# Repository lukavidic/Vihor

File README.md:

# Vihor

Autonomna mobilna platforma sa integrisanim elektromagnetskim topom. Vozilo se zasniva na JoyCar platformi (Joy-IT), a naša ploča (PCB) zamjenjuje micro:bit i upravlja kretanjem, senzorima, topom i WiFi komunikacijom. Vozilo autonomno traži i gađa pokretnu metu na suparničkom vozilu istog tipa, izbjegava prepreke, a START/STOP i log poruke ide preko WiFi-ja do aplikacije na računaru.

Projekat iz računarske elektronike (RE/MKS 26/27).

## Sistem u kratkim crtama

| Dio | Opis |
|---|---|
| Mikrokontroler | PIC24FJ64GA702 |
| WiFi | ESP8266 (ESP-01), AT komande preko UART-a |
| Senzori | HC-SR04 (prepreke), IR Distance Click (meta) |
| Vozilo | JoyCar (motori i drajveri na JoyCar ploči, I2C) |
| Napajanje | 4 × AA baterije, naponi sa zaglavlja JoyCar ploče |
| Top | Elektromagnetski top (coilgun), još nije isporučen |
| Aplikacija | Java (JavaFX), TCP server, komande START i STOP, prikaz logova |

## Dokumentacija

| Dokument | Sadržaj |
|---|---|
| [Specifikacija zahtjeva](docs/Specifikacija-zahtjeva.md) | Funkcionalni i nefunkcionalni zahtjevi, mašine stanja, format logova |
| [HW/SW interfejs](docs/architecture/hwsw-interface.md) | Napajanje, pinovi mikrokontrolera, JoyCar interfejs, komunikacioni protokol |
| [Hardverska arhitektura](docs/architecture/hardware.md) | Blok dijagram, napajanje, konektori, mjerenja |
| [Softverska arhitektura](docs/architecture/software.md) | Moduli firmvera, mašine stanja, aplikacija |
| [Spisak komponenti](docs/components.md) | Sve komponente sa slikama i osnovnim podacima |
| [Električna šema (PDF)](docs/Vihor.pdf) | Svi listovi šeme: naslovni list, blok šema i moduli |

## Organizacija rada

- Zadaci se vode na GitHub Projects tabli **Vihor SCRUM Board**, svaki zadatak je issue sa labelom `hardware` ili `software`.
- Grana `main` sadrži stabilnu verziju, a rad se objedinjuje u granu `dev`.
- Za svaki zadatak se pravi nova grana iz `dev`, imenovana kao `<broj-issuea>-kratak-opis` (npr. `3-hardverska-arhitektura-sistema`).
- Izmjene idu preko Pull Requesta prema `dev`, uz pregled barem jedne osobe. U opisu se navodi `Refs #<broj>`, a issue se zatvara ručno kad je zadatak gotov.
- Dokumenti nose broj verzije u zaglavlju, a ne u imenu grane ili fajla.

## Struktura repozitorija

```
.
├── README.md
├── LICENSE
├── .gitattributes              podešavanja gita za KiCad fajlove
├── .github/                    šabloni za issue i pull request
├── docs/
│   ├── Specifikacija-zahtjeva.md
│   ├── components.md
│   ├── Vihor.pdf               električna šema (svi listovi)
│   ├── images/                 slike komponenti
│   ├── resources/              dijagrami (mašine stanja, aktivnosti)
│   └── architecture/
│       ├── hwsw-interface.md
│       ├── hardware.md
│       └── software.md
├── hardware/
│   ├── Vihor/                  KiCad projekat (šema i ploča)
│   └── libs/                   simboli, footprinti i 3D modeli (PIC, ESP-01, ivični konektor)
└── firmware/
    └── tests/                  testni programi za EasyPIC i TCP server za test na računaru
```

Aplikacija dobija svoj folder (npr. `app/`) kad se doda u repozitorij.

## Stanje projekta

- **Dokumentacija:** specifikacija zahtjeva, HW/SW interfejs, hardverska arhitektura i spisak komponenti su usklađeni sa šemom i rezultatima mjerenja. 
- **Šema:** pripremljena za izradu ploče (PR #47); vrijednosti dijelova za top (R5, R7, D1, F1) još nisu određene.
- **Ispitivanje dijelova:** na razvojnoj ploči EasyPIC Fusion v7 (umjesto našeg PIC-a) ispitani su ESP-01 (AT komande, WiFi, TCP, START i STOP), motori preko I2C i servo motor; testni programi su u `firmware/tests/`. IR senzor je izmjeren multimetrom (napon izlaza u zavisnosti od udaljenosti), a kod ultrazvučnog senzora su izmjereni signali TRIG i ECHO na JoyCar ploči. Rezultati su u `docs/architecture/hwsw-interface.md`.
- **Top:** još nije isporučen; interfejs je predviđen na ploči.

## Licenca

Vidi [LICENSE](LICENSE).

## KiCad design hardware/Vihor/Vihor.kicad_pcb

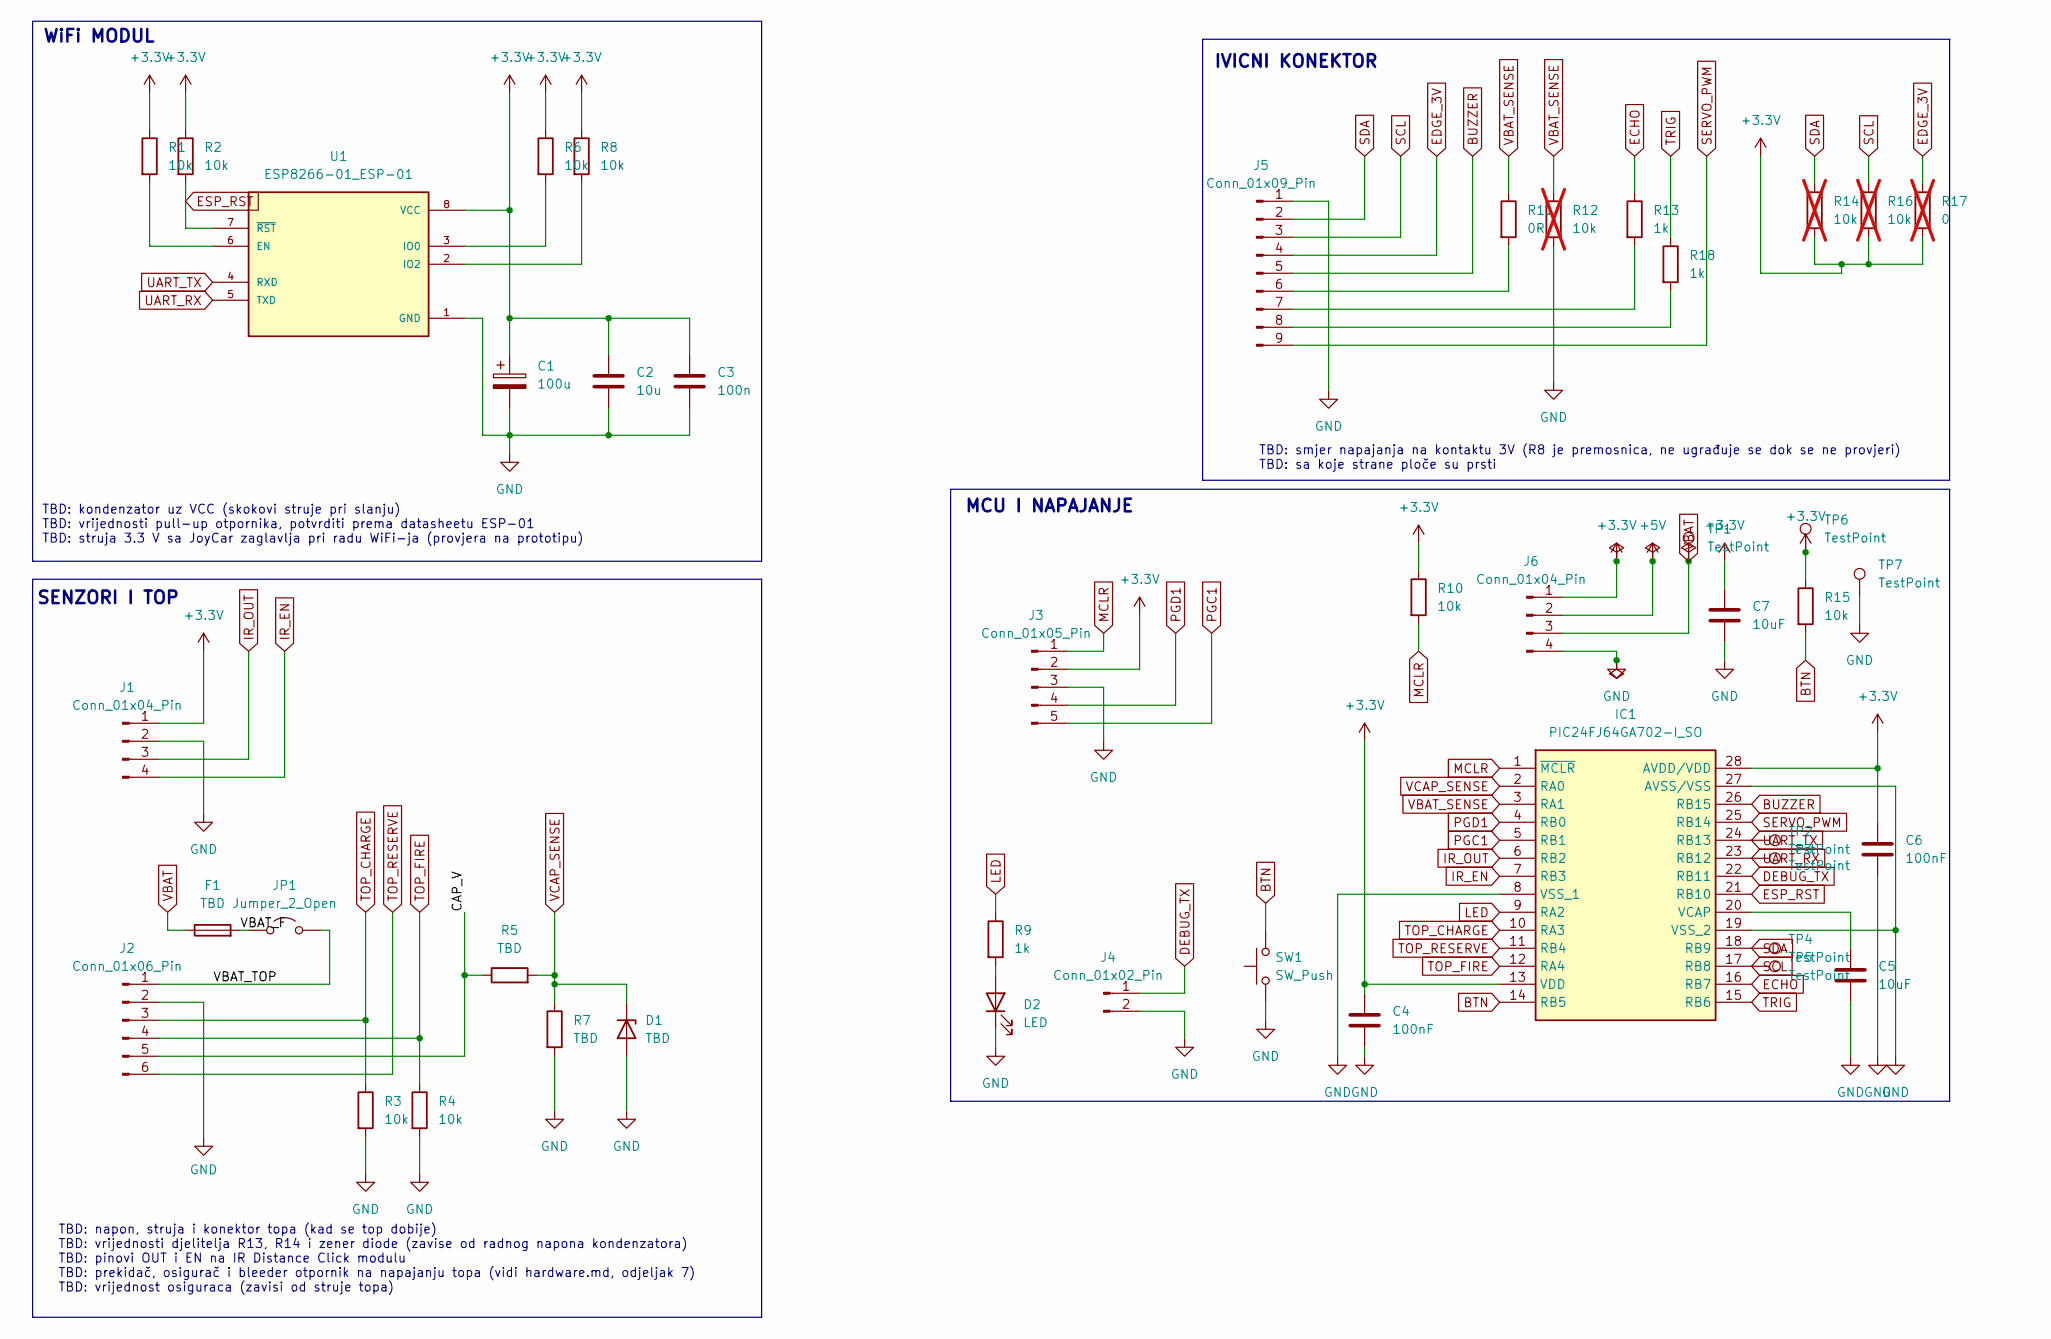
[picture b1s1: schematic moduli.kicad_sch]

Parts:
C1: 100u; CP_Radial_D6.3mm_P2.50mm
C2: 10u; C_0805_2012Metric
C3: 100n; C_0805_2012Metric
C4, C6: 100nF; C_0805_2012Metric
C5, C7: 10uF; C_0805_2012Metric
D1: TBD; D_SOD-123
D2: LED; LED_0805_2012Metric
F1: TBD; Fuse_1206_3216Metric
IC1: PIC24FJ64GA702-I_SO; SOIC127P1030X265-28N; Mouser Part Number 579-24FJ64GA702ISO
J1, J6: Conn_01x04_Pin; PinHeader_1x04_P2.54mm_Vertical
J2: Conn_01x06_Pin; PinHeader_1x06_P2.54mm_Vertical
J3: Conn_01x05_Pin; PinHeader_1x05_P2.54mm_Vertical
J4: Conn_01x02_Pin; PinHeader_1x02_P2.54mm_Vertical
J5: Conn_01x09_Pin; MicroBit_EdgeFingers_9
JP1: Jumper_2_Open; PinHeader_1x02_P2.54mm_Vertical
R1, R2, R3, R4, R6, R8, R10, R15: 10k; R_0805_2012Metric
R5, R7: TBD; R_0805_2012Metric
R9, R13, R18: 1k; R_0805_2012Metric
R11: 0R; R_0805_2012Metric
R12, R14, R16: 10k; R_0805_2012Metric; not fitted
R17: 0; R_0805_2012Metric; not fitted
SW1: SW_Push; SW_PUSH_6mm
TP1, TP2, TP3, TP4, TP5, TP6: TestPoint; TestPoint_Pad_D1.5mm
TP7: TestPoint; TestPoint_THTPad_D2.0mm_Drill1.0mm
U1: ESP8266-01_ESP-01; ESP-01_Socket_2x04_P2.54mm; PARTREV V1.2

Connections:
+3.3V: C1.1, C2.1, C3.1, C4.1, C6.1, C7.1, IC1.13 (VDD), IC1.28 (AVDD/VDD), J1.1, J3.2, J6.1, R1.1, R2.1, R6.1, R8.1, R10.1, R14.2, R15.1, R16.2, R17.2, TP6.1 (1_1), U1.8 (VCC)
+5V: J6.2
/Moduli/CAP_V: J2.5, R5.1
/Moduli/VBAT_F: F1.2, JP1.1 (A)
/Moduli/VBAT_TOP: J2.1, JP1.2 (B)
BTN: IC1.14 (RB5), R15.2, SW1.2
BUZZER: IC1.26 (RB15), J5.5
DEBUG_TX: IC1.22 (RB11), J4.1
ECHO: IC1.16 (RB7), R13.1
EDGE_3V: J5.4, R17.1
ESP_RST: IC1.21 (RB10), R2.2, U1.7 (~RST)
GND: C1.2, C2.2, C3.2, C4.2, C5.2, C6.2, C7.2, D1.2 (A), D2.1 (K), IC1.8 (VSS_1), IC1.19 (VSS_2), IC1.27 (AVSS/VSS), J1.2, J2.2, J3.3, J4.2, J5.1, J6.4, R3.2, R4.2, R7.2, R12.2, SW1.1, TP7.1 (1_1), U1.1 (GND)
IR_EN: IC1.7 (RB3), J1.4
IR_OUT: IC1.6 (RB2), J1.3
LED: IC1.9 (RA2), R9.1
MCLR: IC1.1 (~MCLR), J3.1, R10.2
unnamed: D2.2 (A), R9.2
unnamed: C5.1, IC1.20 (VCAP)
unnamed: J5.6, R11.2
unnamed: J5.7, R13.2
unnamed: J5.8, R18.2
unnamed: R1.2, U1.6 (EN)
unnamed: R6.2, U1.3 (IO0)
unnamed: R8.2, U1.2 (IO2)
PGC1: IC1.5 (RB1), J3.5
PGD1: IC1.4 (RB0), J3.4
SCL: IC1.17 (RB8), J5.3, R16.1, TP5.1 (1_1)
SDA: IC1.18 (RB9), J5.2, R14.1, TP4.1 (1_1)
SERVO_PWM: IC1.25 (RB14), J5.9
TOP_CHARGE: IC1.10 (RA3), J2.3, R3.1
TOP_FIRE: IC1.12 (RA4), J2.4, R4.1
TOP_RESERVE: IC1.11 (RB4), J2.6
TRIG: IC1.15 (RB6), R18.1
UART_RX: IC1.23 (RB12), TP3.1 (1_1), U1.5 (TXD)
UART_TX: IC1.24 (RB13), TP2.1 (1_1), U1.4 (RXD)
VBAT: F1.1, J6.3, TP1.1 (1_1)
VBAT_SENSE: IC1.3 (RA1), R11.1, R12.1
VCAP_SENSE: D1.1 (K), IC1.2 (RA0), R5.2, R7.1

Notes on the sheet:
TBD: napon, struja i konektor topa (kad se top dobije) TBD: vrijednosti djelitelja R13, R14 i zener diode (zavise od radnog napona kondenzatora) TBD: pinovi OUT i EN na IR Distance Click modulu TBD: prekidač, osigurač i bleeder otpornik na napajanju topa (vidi hardware.md, odjeljak 7) TBD: vrijedno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
TBD: smjer napajanja na kontaktu 3V (R8 je premosnica, ne ugrađuje se dok se ne provjeri) TBD: sa koje strane ploče su prsti
IVICNI KONEKTOR
SENZORI I TOP
TBD: kondenzator uz VCC (skokovi struje pri slanju) TBD: vrijednosti pull-up otpornika, potvrditi prema datasheetu ESP-01 TBD: struja 3.3 V sa JoyCar zaglavlja pri radu WiFi-ja (provjera na prototipu)
WiFi MODUL
MCU I NAPAJANJE

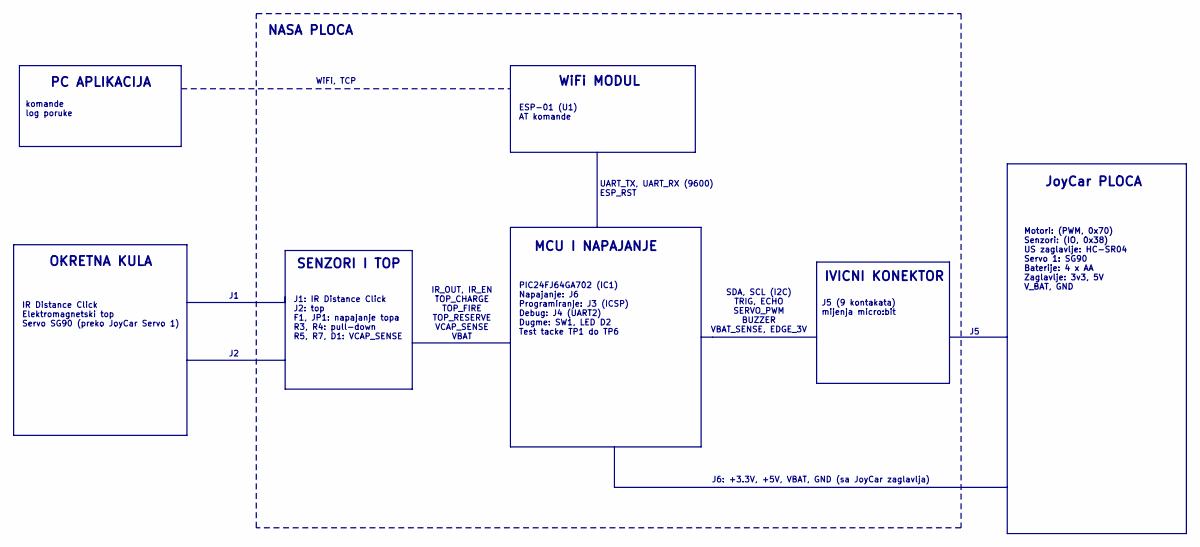
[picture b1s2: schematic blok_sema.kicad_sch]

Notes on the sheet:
MCU I NAPAJANJE
OKRETNA KULA
IR Distance Click Elektromagnetski top Servo SG90 (preko JoyCar Servo 1)
SENZORI I TOP
ESP-01 (U1) AT komande
IVICNI KONEKTOR
PC APLIKACIJA
J6: +3.3V, +5V, VBAT, GND (sa JoyCar zaglavlja)
JoyCar PLOCA
IR_OUT, IR_EN TOP_CHARGE TOP_FIRE TOP_RESERVE VCAP_SENSE VBAT
UART_TX, UART_RX (9600) ESP_RST
J1: IR Distance Click J2: top F1, JP1: napajanje topa R3, R4: pull-down R5, R7, D1: VCAP_SENSE
NASA PLOCA
SDA, SCL (I2C) TRIG, ECHO SERVO_PWM BUZZER VBAT_SENSE, EDGE_3V
komande log poruke
J5 (9 kontakata) mijenja micro:bit
Motori: (PWM, 0x70) Senzori: (IO, 0x38) US zaglavlje: HC-SR04 Servo 1: SG90 Baterije: 4 x AA Zaglavlje: 3v3, 5V V_BAT, GND
PIC24FJ64GA702 (IC1) Napajanje: J6 Programiranje: J3 (ICSP) Debug: J4 (UART2) Dugme: SW1, LED D2 Test tacke TP1 do TP6
WiFi MODUL
WiFi, TCP

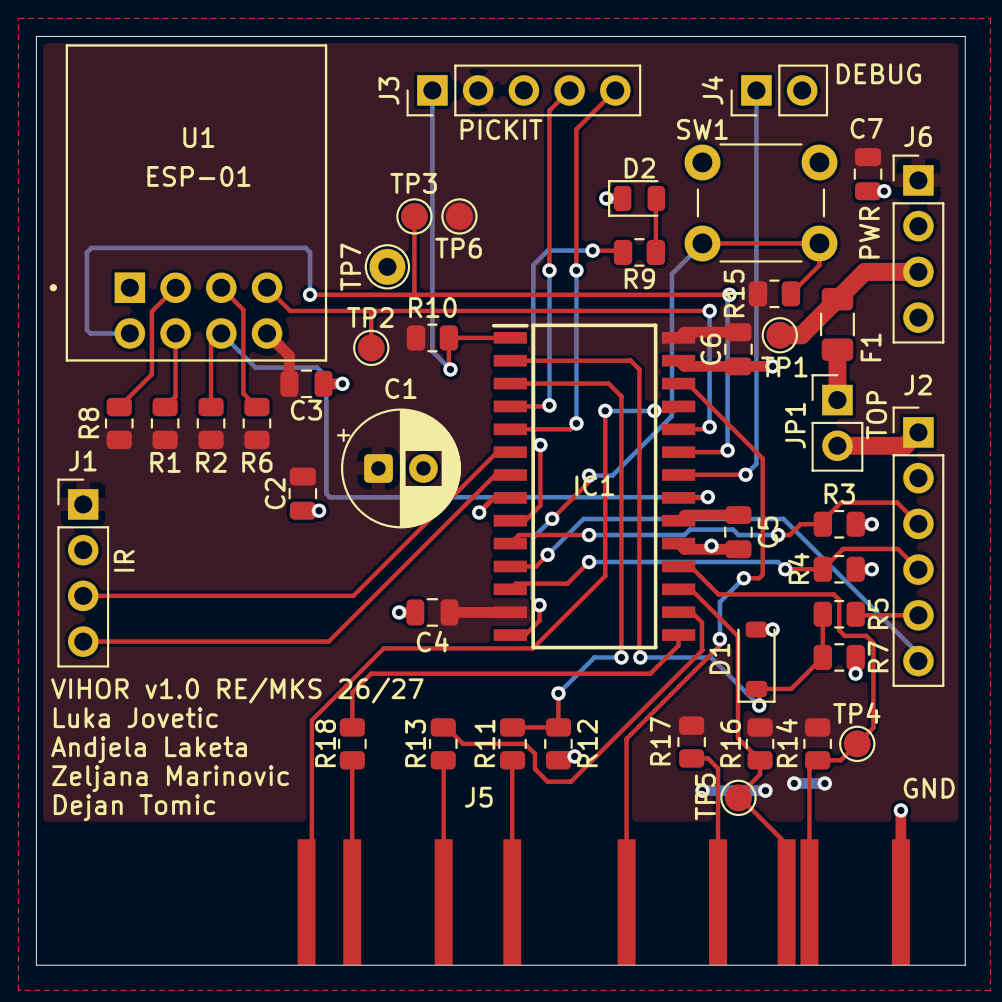
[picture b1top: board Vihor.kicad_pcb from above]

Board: 2 copper layers, 51.6 x 51.6 mm, 45 parts (0 on the bottom side), 37 nets.
